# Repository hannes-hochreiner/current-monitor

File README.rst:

.. image:: images/rendering_front.png
    :align: center
    :alt: rendering of the pcb

Current Monitor
~~~~~~~~~~~~~~~

A simple current monitor.

Requirements
============

Measure the current in the range of 150 mA to 1 µA (about 104 dB dynamic range) on a 100 µs (10 kHz) timescale.

Main Parts
==========

Current Sense Element
---------------------

ZXCT1110W5-7
............

`Datasheet <https://www.diodes.com/assets/Datasheets/ZXCT1107_10.pdf>`_

+------------------------+-------------------+
|Manufacturer            |Diodes Incorporated|
+------------------------+-------------------+
|Manufacturer Part Number|ZXCT1110W5-7       |
+------------------------+-------------------+
|Digi-Key Part Number    |ZXCT1110W5-7DICT-ND|
+------------------------+-------------------+

+------------+----------------------------+-------------------------+
|Parameter   |Equation                    |Value                    |
+============+============================+=========================+
|V_sense_max |                            | 0.3 V                   |
+------------+----------------------------+-------------------------+
|I_sense_max |                            | 0.15 A                  |
+------------+----------------------------+-------------------------+
|R_sense     | V / I                      | 2 Ohm                   |
+------------+----------------------------+-------------------------+
|I_out_max   | 4e-3 A/V * V_sense_max     | 1.2 mA                  |
+------------+----------------------------+-------------------------+
|R_gain      | ADC_full_scale / I_out_max | 1.2 V / 1.2 mA = 1 kOhm |
+------------+----------------------------+-------------------------+
|Gain        | V_out/V_sense              | 1.2 / 0.3 = 4           |
+------------+----------------------------+-------------------------+
|            | 2 V_sense / I_sense        |                         |
+------------+----------------------------+-------------------------+

INA381
......

`Datasheet <https://www.ti.com/lit/ds/symlink/ina381.pdf>`_

+--------------------------+---------------------------------+
| Manufacturer             | Texas Instruments               |
+--------------------------+---------------------------------+
| Manufacturer Part Number | INA381A1IDSGR                   |
+--------------------------+---------------------------------+
| Digi-Key Part Number     | 296-50475-1-ND                  |
+--------------------------+---------------------------------+

+------------+-----------------------------------+------------+
|Parameter   |Equation                           |Value       |
+============+===================================+============+
|I_sense_max |                                   | 0.15 A     |
+------------+-----------------------------------+------------+
|R_sense     | V_full_scale / gain / I_sense_max | 0.4 Ohm    |
+------------+-----------------------------------+------------+
|V_sense_max | I_sense_max * R_sense             | 0.06 V     |
+------------+-----------------------------------+------------+
|V_out_max   | I_sense_max * R_sense * gain      | 1.2 V      |
+------------+-----------------------------------+------------+

Others
......

https://datasheets.maximintegrated.com/en/ds/MAX9934.pdf

ADC
---

ADS131M04
.........

`Datasheet <https://www.ti.com/lit/ds/symlink/ads131m04.pdf>`_

+--------------------------+------------------------+
| Manufacturer             | Texas Instruments      |
+--------------------------+------------------------+
| Manufacturer Part Number | ADS131M04IPWR          |
+--------------------------+------------------------+
| Digi-Key Part Number     | 296-ADS131M04IPWRCT-ND	|
+--------------------------+------------------------+

+----------------------+-----------+
| Parameter            | Value     |
+======================+===========+
| full-scale           | 0-1.2 V   |
+----------------------+-----------+
| OSR                  | 256       |
+----------------------+-----------+
| CLKIN                | 8.192 MHz |
+----------------------+-----------+
| data rate            | 16 kHz    |
+----------------------+-----------+
| effective resolution | 17.8 bit  |
+----------------------+-----------+
| SPI clock            | > 2.5 MHz |
+----------------------+-----------+

min Voltage = 1.2 / Math.pow(2,24) * Math.pow(2,24-17.8) * 1e6 = 10.5 µV => 0.65 µA lower limit

Clock
-----

SIT1602BI
.........

+--------------------------+------------------------------------+
| Manufacturer             | SiTime                             |
+--------------------------+------------------------------------+
| Manufacturer Part Number | SIT1602BI-21-XXE-8.192000G         |
+--------------------------+------------------------------------+
| Digi-Key Part Number     | 1473-SIT1602BI-21-XXE-8.192000G-ND |
+--------------------------+------------------------------------+

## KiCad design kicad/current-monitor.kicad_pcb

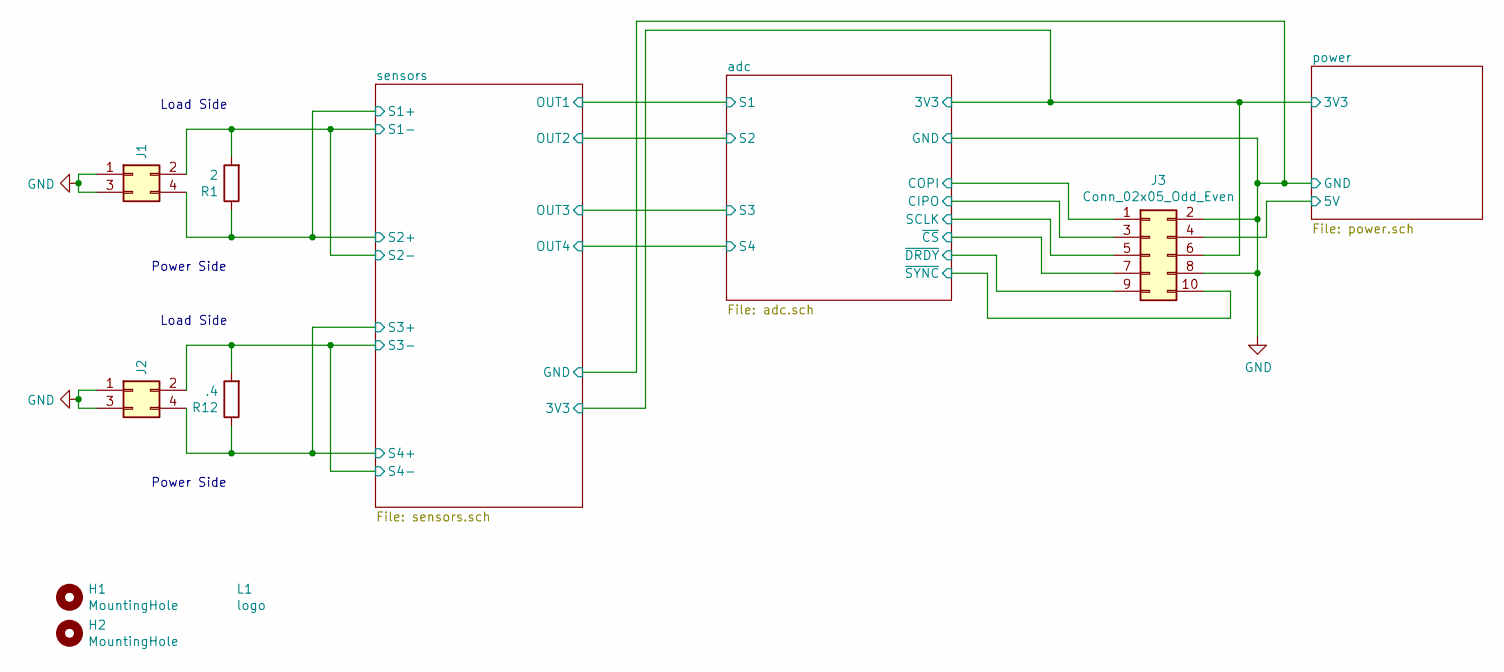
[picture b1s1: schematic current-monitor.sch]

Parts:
H1, H2: MountingHole; MountingHole_2.2mm_M2_Pad_Via
J1, J2: Conn_02x02_Odd_Even; PinHeader_2x02_P2.54mm_Vertical_SMD
J3: Conn_02x05_Odd_Even; PinHeader_2x05_P2.54mm_Vertical_SMD; Manufacturer Part Number 10129383-910002ALF; Digi-Key Part Number 609-10129383-910002ALFCT-ND
L1: logo
R1: 2; R_0612_1632Metric; Manufacturer Part Number LTR18EZPF2R00; Digi-Key Part Number RHM2YCT-ND
R12: .4; R_2010_5025Metric; Manufacturer Part Number WSLT2010R4000FEB18; Digi-Key Part Number WSLTA-.400CT-ND

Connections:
/adc/3V3: J3.6; also elsewhere on the board
/adc/CIPO: J3.3; also elsewhere on the board
/adc/COPI: J3.1; also elsewhere on the board
/adc/SCLK: J3.5; also elsewhere on the board
/adc/~CS: J3.7; also elsewhere on the board
/adc/~DRDY: J3.9; also elsewhere on the board
/adc/~SYNC: J3.10; also elsewhere on the board
/power/5V: J3.4; also elsewhere on the board
/sensors/S1+: J1.4, R1.1; also elsewhere on the board
/sensors/S1-: J1.2, R1.2; also elsewhere on the board
/sensors/S3+: J2.4, R12.1; also elsewhere on the board
/sensors/S3-: J2.2, R12.2; also elsewhere on the board
GND: J1.1, J1.3, J2.1, J2.3, J3.2, J3.8; also elsewhere on the board

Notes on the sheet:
Power Side
Load Side

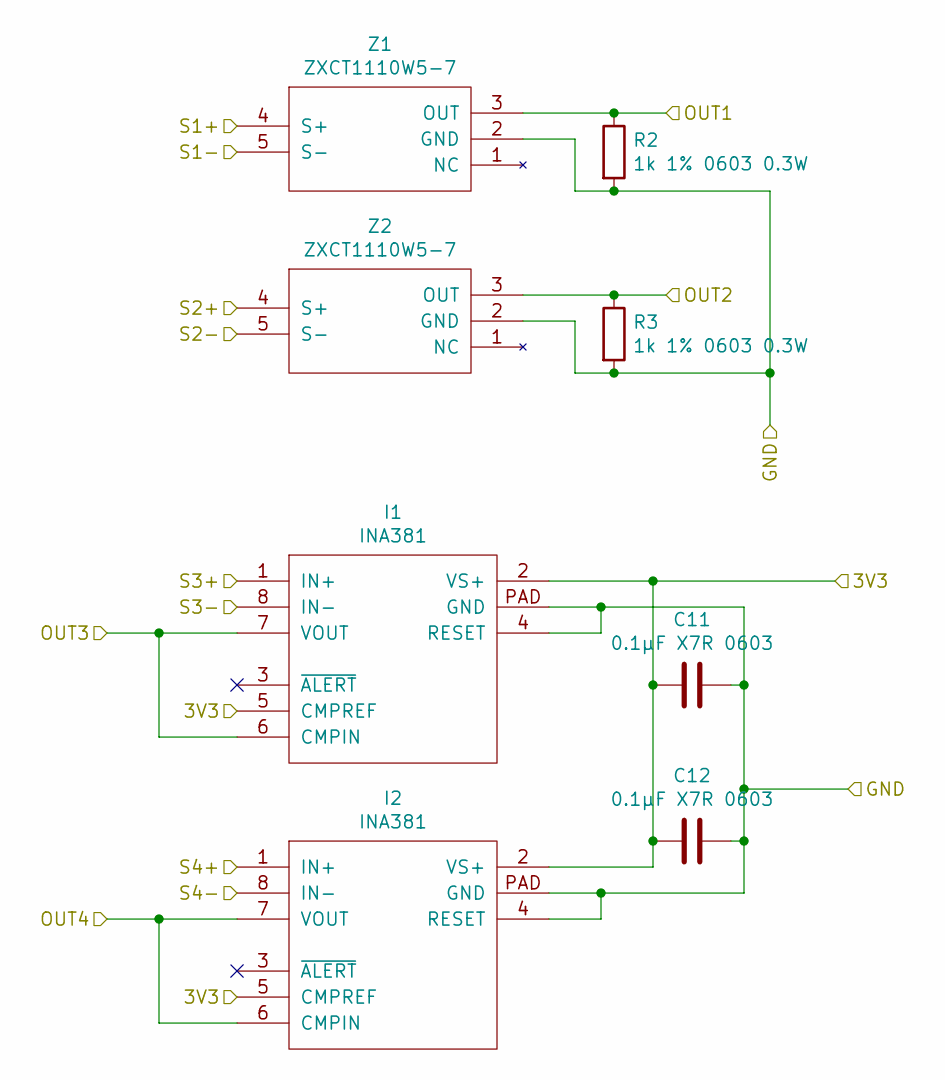
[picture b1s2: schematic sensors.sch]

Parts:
C11, C12: 0.1µF X7R 0603; C_0603_1608Metric
I1, I2: INA381; INA381-WSON; Manufacturer Part Number INA381A1IDSGR; Digi-Key Part Number 296-50475-1-ND
R2, R3: 1k 1% 0603 0.3W; R_0603_1608Metric
Z1, Z2: ZXCT1110W5-7; SOT-23-5; Manufacturer Part Number ZXCT1110W5-7; Digi-Key Part Number ZXCT1110W5-7DICT-ND

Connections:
/adc/3V3: C11.2, C12.2, I1.2 (VS+), I1.5 (CMPREF), I2.2 (VS+), I2.5 (CMPREF); also elsewhere on the board
/sensors/OUT1: R2.1, Z1.3 (OUT); also elsewhere on the board
/sensors/OUT2: R3.1, Z2.3 (OUT); also elsewhere on the board
/sensors/OUT3: I1.6 (CMPIN), I1.7 (VOUT); also elsewhere on the board
/sensors/OUT4: I2.6 (CMPIN), I2.7 (VOUT); also elsewhere on the board
/sensors/S1+: Z1.4 (S+), Z2.4 (S+); also elsewhere on the board
/sensors/S1-: Z1.5 (S-), Z2.5 (S-); also elsewhere on the board
/sensors/S3+: I1.1 (IN+), I2.1 (IN+); also elsewhere on the board
/sensors/S3-: I1.8 (IN-), I2.8 (IN-); also elsewhere on the board
GND: C11.1, C12.1, I1.4 (RESET), I1.PAD (GND), I2.4 (RESET), I2.PAD (GND), R2.2, R3.2, Z1.2 (GND), Z2.2 (GND); also elsewhere on the board

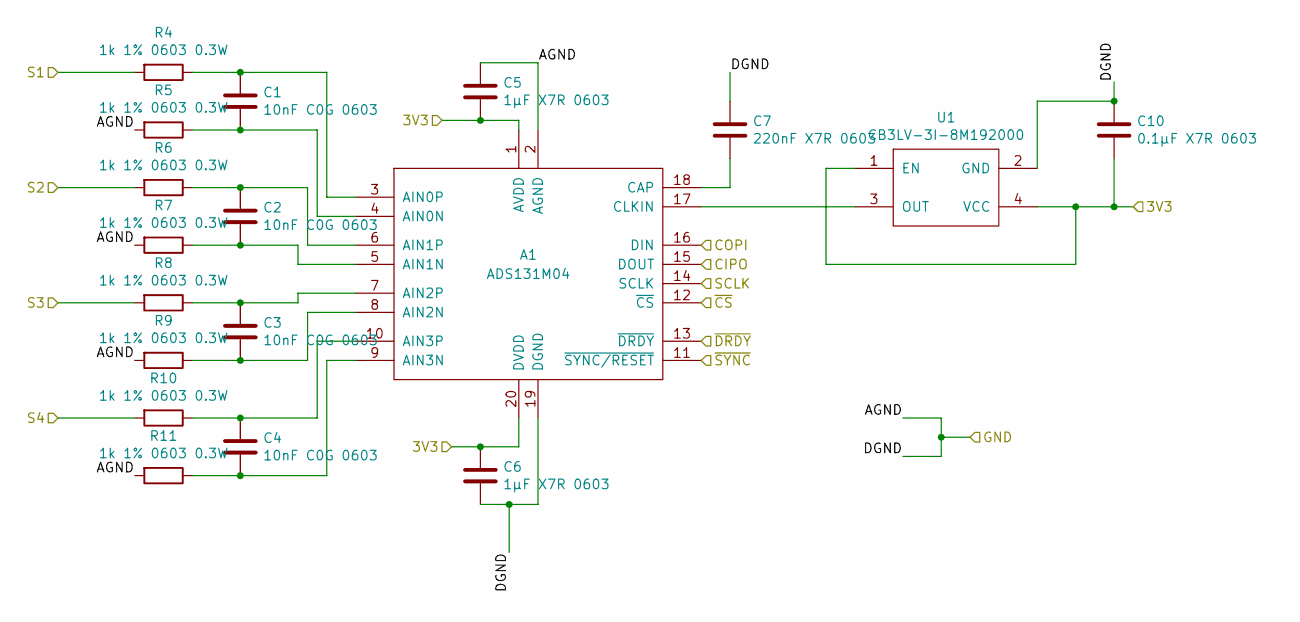
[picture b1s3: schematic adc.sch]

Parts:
A1: ADS131M04; TSSOP-20_4.4x6.5mm_P0.65mm; Manufacturer Part Number ADS131M04IPWR; Digi-Key Part Number 296-ADS131M04IPWRCT-ND
C1, C2, C3, C4: 10nF C0G 0603; C_0603_1608Metric
C5, C6: 1µF X7R 0603; C_0603_1608Metric
C7: 220nF X7R 0603; C_0603_1608Metric
C10: 0.1µF X7R 0603; C_0603_1608Metric
R4, R5, R6, R7, R8, R9, R10, R11: 1k 1% 0603 0.3W; R_0603_1608Metric
U1: CB3LV-3I-8M192000; Manufacturer Part Number CB3LV-3I-8M192000; Digi-Key Part Number 110-CB3LV-3I-8M192000CT-ND

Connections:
/adc/3V3: A1.1 (AVDD), A1.20 (DVDD), C5.2, C6.1, C10.2, U1.1 (EN), U1.4 (VCC); also elsewhere on the board
/adc/CIPO: A1.15 (DOUT); also elsewhere on the board
/adc/COPI: A1.16 (DIN); also elsewhere on the board
/adc/SCLK: A1.14 (SCLK); also elsewhere on the board
/adc/~CS: A1.12 (~CS); also elsewhere on the board
/adc/~DRDY: A1.13 (~DRDY); also elsewhere on the board
/adc/~SYNC: A1.11 (~SYNC/RESET); also elsewhere on the board
/sensors/OUT1: R4.2; also elsewhere on the board
/sensors/OUT2: R6.2; also elsewhere on the board
/sensors/OUT3: R8.2; also elsewhere on the board
/sensors/OUT4: R10.2; also elsewhere on the board
GND: A1.2 (AGND), A1.19 (DGND), C5.1, C6.2, C7.1, C10.1, R5.2, R7.2, R9.2, R11.2, U1.2 (GND); also elsewhere on the board
unnamed: A1.3 (AIN0P), C1.1, R4.1
unnamed: A1.4 (AIN0N), C1.2, R5.1
unnamed: A1.5 (AIN1N), C2.2, R7.1
unnamed: A1.6 (AIN1P), C2.1, R6.1
unnamed: A1.7 (AIN2P), C3.1, R8.1
unnamed: A1.8 (AIN2N), C3.2, R9.1
unnamed: A1.9 (AIN3N), C4.2, R11.1
unnamed: A1.10 (AIN3P), C4.1, R10.1
unnamed: A1.17 (CLKIN), U1.3 (OUT)
unnamed: A1.18 (CAP), C7.2

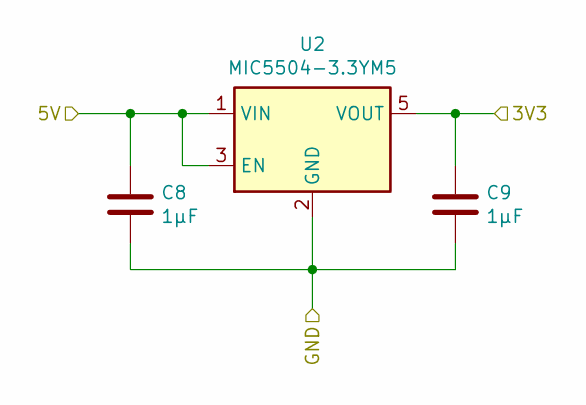
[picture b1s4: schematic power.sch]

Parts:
C8, C9: 1µF; C_0603_1608Metric
U2: MIC5504-3.3YM5; SOT-23-5

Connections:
/adc/3V3: C9.1, U2.5 (VOUT); also elsewhere on the board
/power/5V: C8.1, U2.1 (VIN), U2.3 (EN); also elsewhere on the board
GND: C8.2, C9.2, U2.2 (GND); also elsewhere on the board

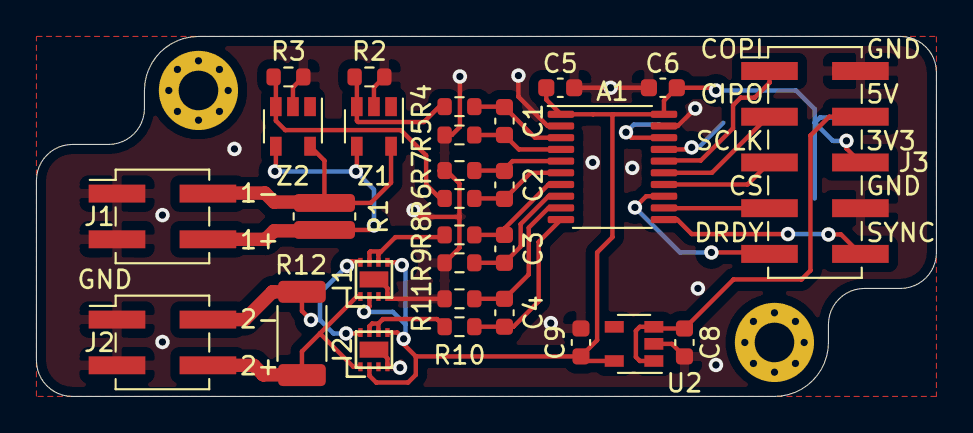
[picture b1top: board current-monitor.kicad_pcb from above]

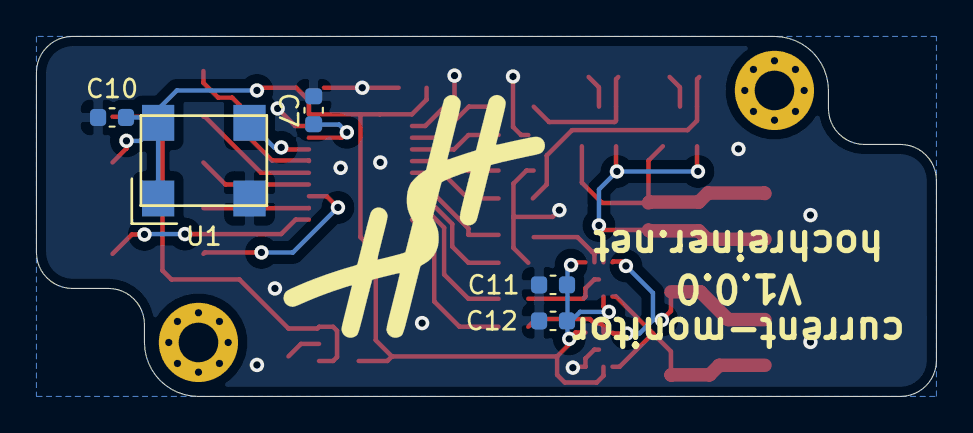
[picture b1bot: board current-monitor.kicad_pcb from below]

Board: 2 copper layers, 50.0 x 20.0 mm, 37 parts (6 on the bottom side), 27 nets.

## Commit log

2020-11-29 fixed links
2020-11-29 started layout
2020-12-03 snapshot
2020-12-03 add second R_sense
2020-12-05 move clock to back
2020-12-06 put markings on pcb
2020-12-06 add rendering
2020-12-06 switch clock and add bypass
2020-12-08 start box design
2020-12-11 finish basic design
